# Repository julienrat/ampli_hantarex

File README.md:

ampli_hantarex
==============

PCB d'un amplificateur de signaux RGB pour Hantarex 9000 (bornes jeutel)

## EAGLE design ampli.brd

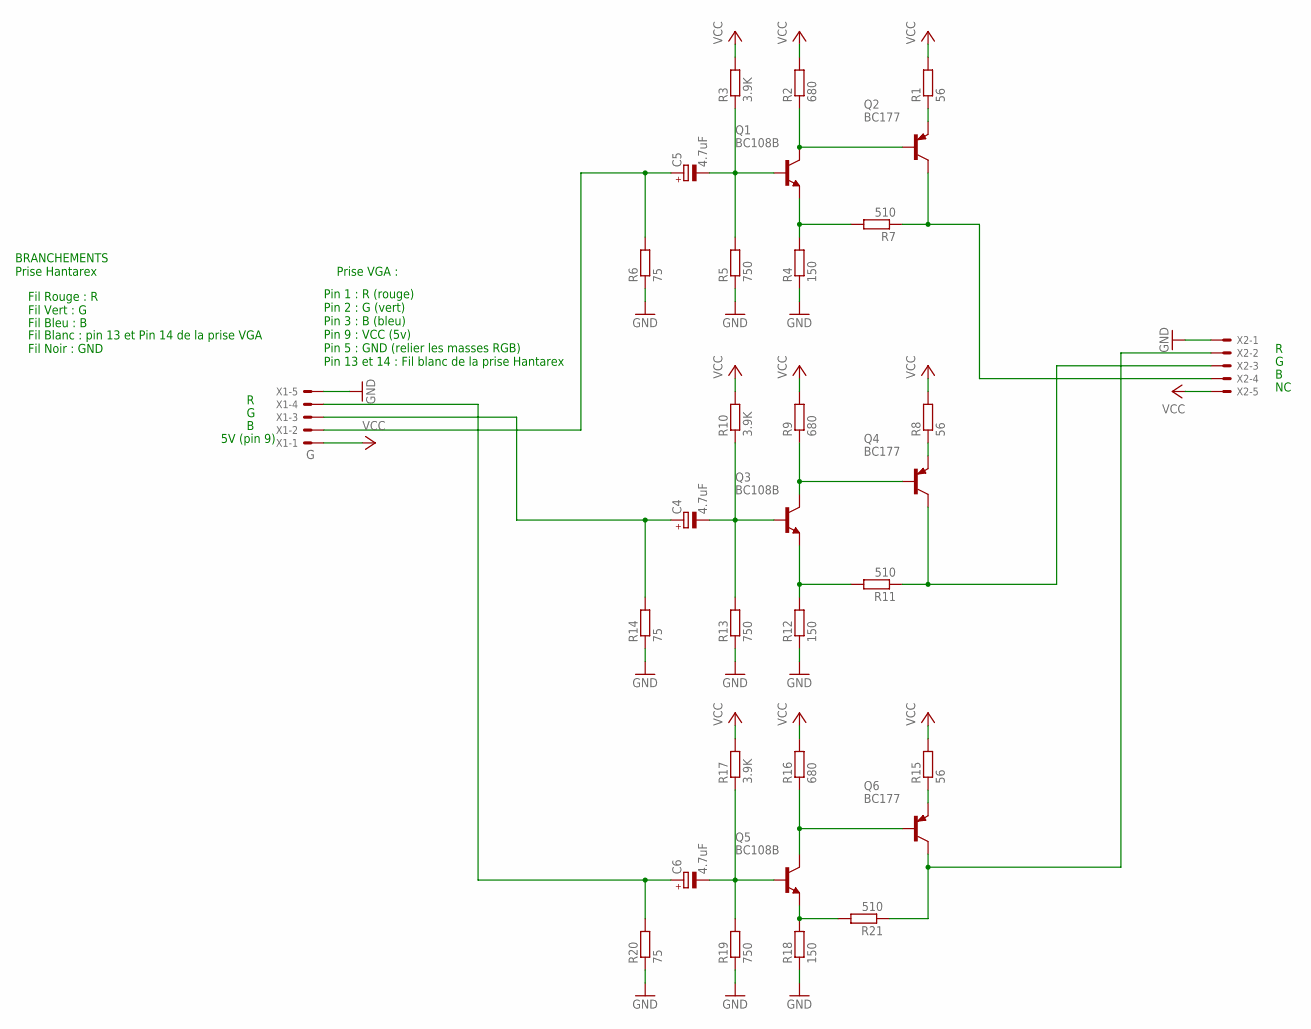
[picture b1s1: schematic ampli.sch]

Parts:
C4, C5, C6: 4.7uF; E5-10,5
Q1, Q3, Q5: BC108B; TO18
Q2, Q4, Q6: BC177; TO18
R1, R8, R15: 56; 0207/10
R2, R9, R16: 680; 0207/10
R3, R10, R17: 3.9K; 0207/10
R4, R12, R18: 150; 0207/10
R5, R13, R19: 750; 0207/10
R6, R14, R20: 75; 0207/10
R7, R11, R21: 510; 0207/10
X1: G; KK-156-5
X2: KK-156-5

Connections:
G: C4.+, R14.2, X1.3
GND: R4.1, R5.1, R6.1, R12.1, R13.1, R14.1, R18.1, R19.1, R20.1, X1.5, X2.1
unnamed: Q1.3 (C), Q2.2 (B), R2.1
unnamed: Q1.1 (E), R4.2, R7.2
unnamed: Q2.3 (C), R7.1, X2.4
unnamed: Q2.1 (E), R1.1
unnamed: C5.-, Q1.2 (B), R3.1, R5.2
unnamed: C6.+, R20.2, X1.4
unnamed: C6.-, Q5.2 (B), R17.1, R19.2
unnamed: Q5.3 (C), Q6.2 (B), R16.1
unnamed: Q5.1 (E), R18.2, R21.2
unnamed: Q6.3 (C), R21.1, X2.2
unnamed: Q6.1 (E), R15.1
unnamed: Q3.1 (E), R11.2, R12.2
unnamed: C4.-, Q3.2 (B), R10.1, R13.2
unnamed: Q3.3 (C), Q4.2 (B), R9.1
unnamed: Q4.3 (C), R11.1, X2.3
unnamed: Q4.1 (E), R8.1
R: C5.+, R6.2, X1.2
VCC: R1.2, R2.2, R3.2, R8.2, R9.2, R10.2, R15.2, R16.2, R17.2, X1.1, X2.5

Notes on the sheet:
5V (pin 9)
BRANCHEMENTS Prise Hantarex
Fil Rouge : R Fil Vert : G
Fil Bleu : B
Fil Blanc : pin 13 et Pin 14 de la prise VGA Fil Noir : GND
Prise VGA :
Pin 1 : R (rouge) Pin 2 : G (vert) Pin 3 : B (bleu) Pin 9 : VCC (5v) Pin 5 : GND (relier les masses RGB) Pin 13 et 14 : Fil blanc de la prise Hantarex

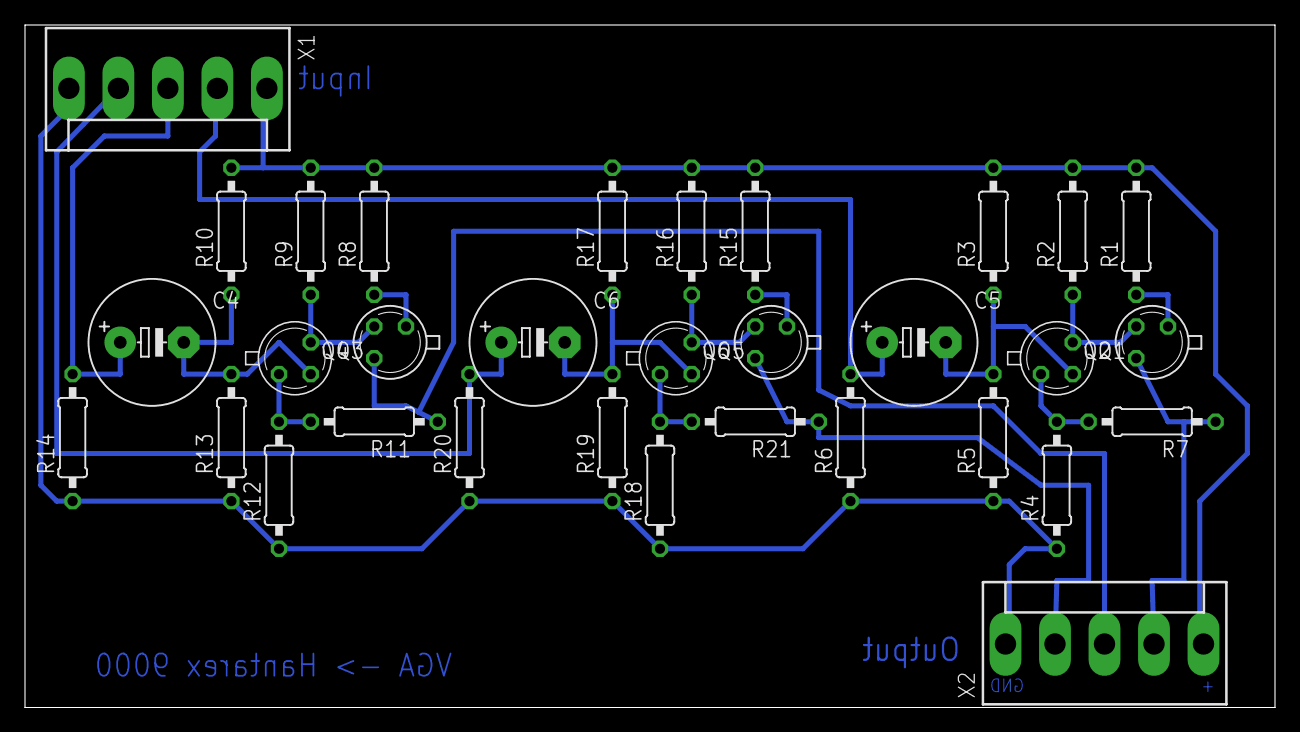
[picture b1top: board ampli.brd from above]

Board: 2 copper layers, 100.0 x 54.6 mm, 32 parts (0 on the bottom side), 20 nets.

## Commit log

2013-12-08 ajout projet ampli Hantarex
2013-12-08 ajout notice
